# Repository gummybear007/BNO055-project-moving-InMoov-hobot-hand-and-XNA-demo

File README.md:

# BNO055-project-moving-InMoov-hobot-hand-and-XNA-demo
Dont know if that can be usefull for something :)

There are videos how that works:

XNA
https://www.youtube.com/watch?v=5ESsEXsImuc

InMoov
https://www.youtube.com/watch?v=VBxMamMVSek

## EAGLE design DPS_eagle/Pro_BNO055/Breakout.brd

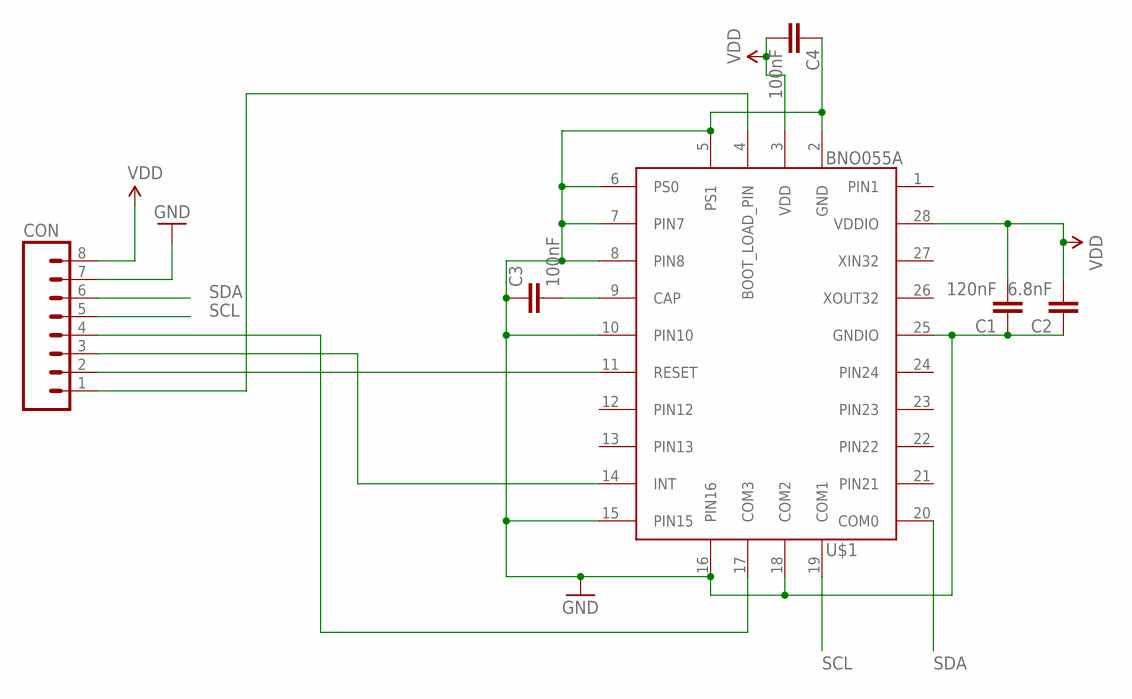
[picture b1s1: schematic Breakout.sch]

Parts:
C1: 120nF; 1206
C2: 6.8nF; 1206
C3, C4: 100nF; 1206
CON: M08NO_SILK; 1X08_NO_SILK
U$1: BNO055A; BNO055

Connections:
GND: C1.1, C2.1, C3.1, C4.1, CON.7, U$1.2 (GND), U$1.5 (PS1), U$1.6 (PS0), U$1.7 (PIN7), U$1.8 (PIN8), U$1.10 (PIN10), U$1.15 (PIN15), U$1.16 (PIN16), U$1.18 (COM2), U$1.25 (GNDIO)
unnamed: CON.2, U$1.11 (RESET)
unnamed: C3.2, U$1.9 (CAP)
unnamed: CON.1, U$1.4 (BOOT_LOAD_PIN)
unnamed: CON.3, U$1.14 (INT)
unnamed: CON.4, U$1.17 (COM3)
SCL: CON.5, U$1.19 (COM1)
SDA: CON.6, U$1.20 (COM0)
VDD: C1.2, C2.2, C4.2, CON.8, U$1.3 (VDD), U$1.28 (VDDIO)

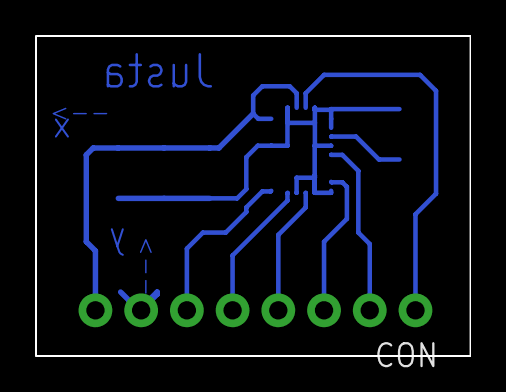
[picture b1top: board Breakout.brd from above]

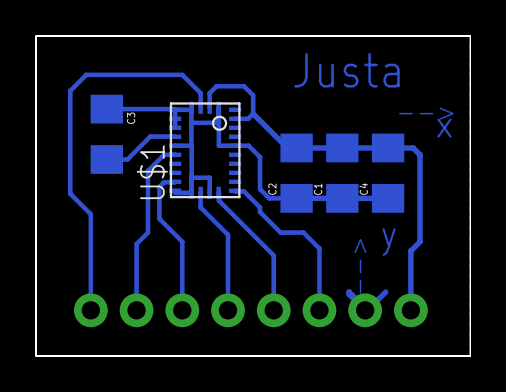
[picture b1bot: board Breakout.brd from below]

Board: 2 copper layers, 24.1 x 17.8 mm, 6 parts (5 on the bottom side), 9 nets.

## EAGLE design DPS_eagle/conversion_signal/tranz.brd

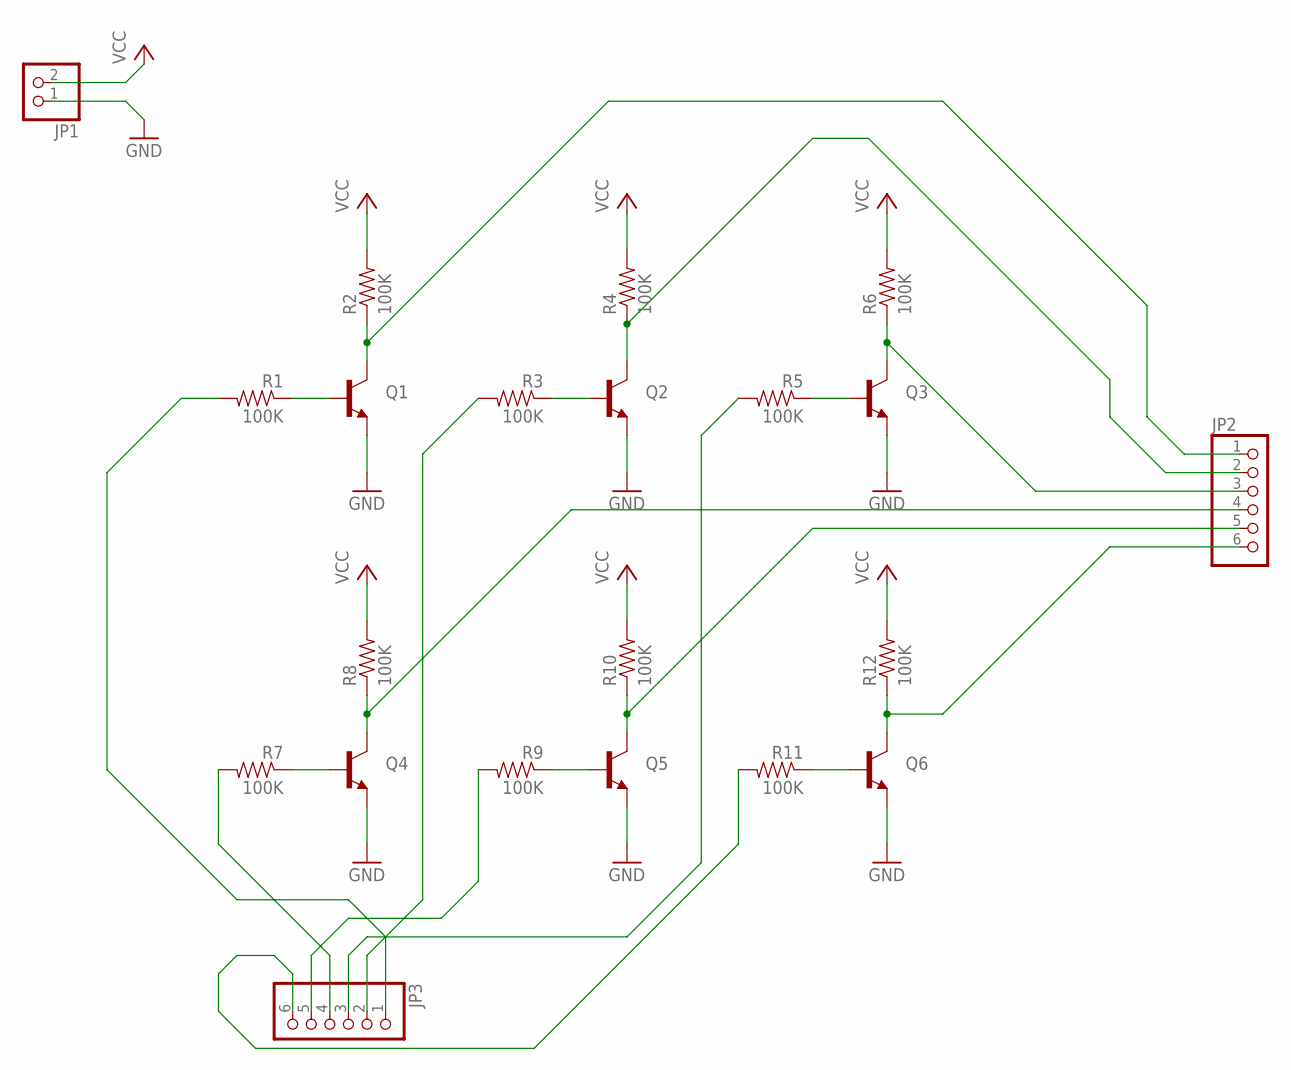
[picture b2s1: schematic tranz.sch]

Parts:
JP1: PINHD-1X2; 1X02
JP2, JP3: PINHD-1X6; 1X06
Q1, Q2, Q3, Q4, Q5, Q6: TRANSISTOR_NPN2N3904; TO-92
R1, R2, R3, R4, R5, R6, R7, R8, R9, R10, R11, R12: 100K; 1206

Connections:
GND: JP1.1, Q1.1 (E), Q2.1 (E), Q3.1 (E), Q4.1 (E), Q5.1 (E), Q6.1 (E)
unnamed: JP3.1, R1.2
unnamed: Q1.2 (B), R1.1
unnamed: JP3.2, R3.2
unnamed: JP3.3, R5.2
unnamed: JP3.4, R7.2
unnamed: JP3.5, R9.2
unnamed: JP3.6, R11.2
unnamed: JP2.1, Q1.3 (C), R2.1
unnamed: JP2.2, Q2.3 (C), R4.1
unnamed: Q2.2 (B), R3.1
unnamed: JP2.3, Q3.3 (C), R6.1
unnamed: Q3.2 (B), R5.1
unnamed: JP2.6, Q6.3 (C), R12.1
unnamed: Q6.2 (B), R11.1
unnamed: Q4.2 (B), R7.1
unnamed: JP2.4, Q4.3 (C), R8.1
unnamed: JP2.5, Q5.3 (C), R10.1
unnamed: Q5.2 (B), R9.1
VCC: JP1.2, R2.2, R4.2, R6.2, R8.2, R10.2, R12.2

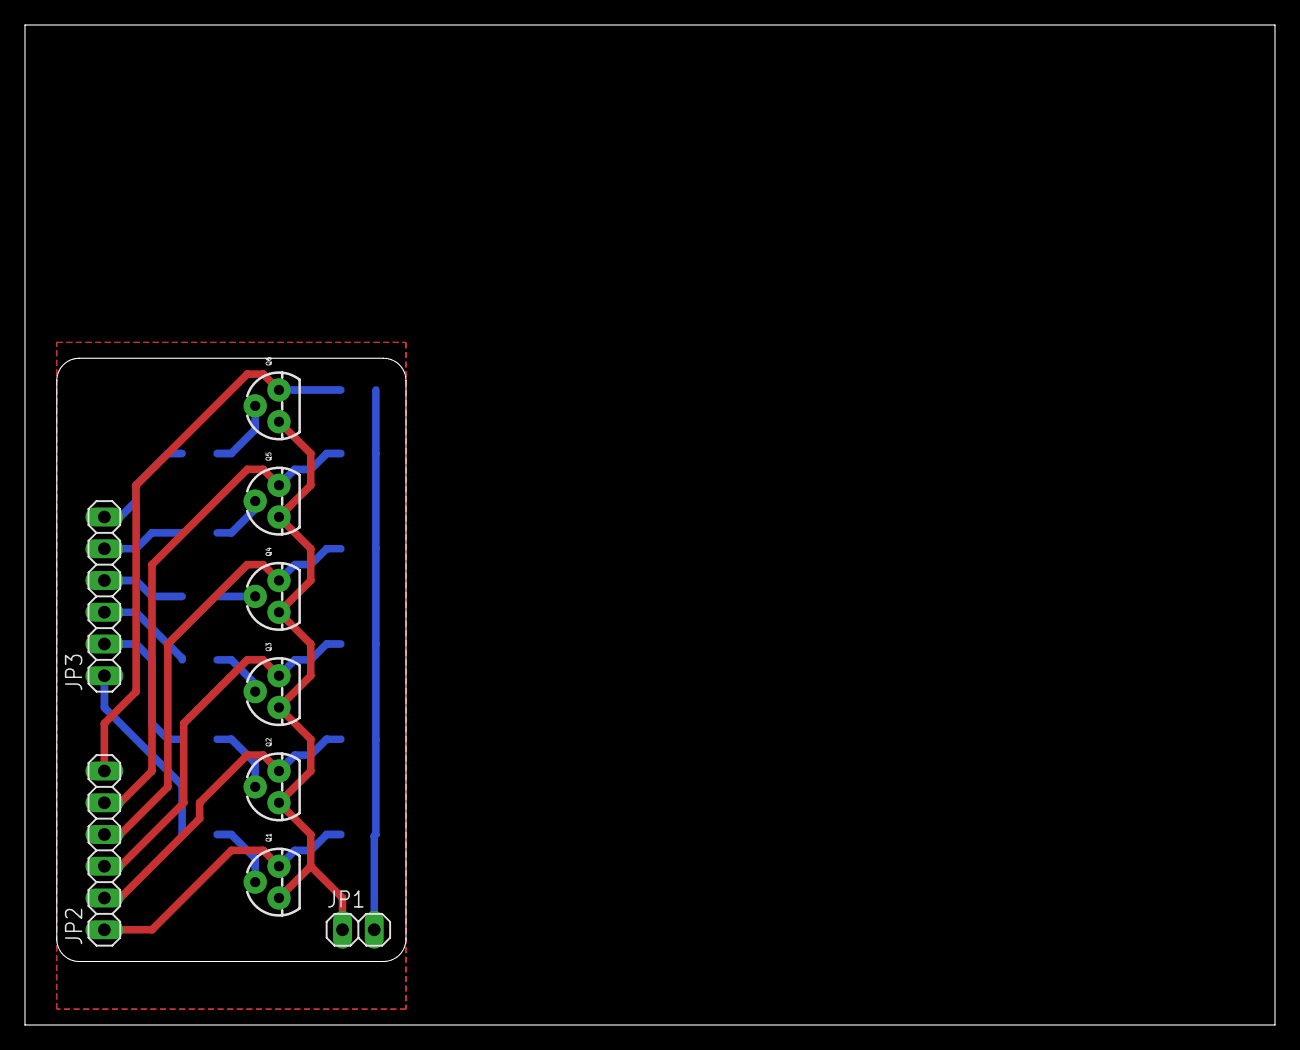
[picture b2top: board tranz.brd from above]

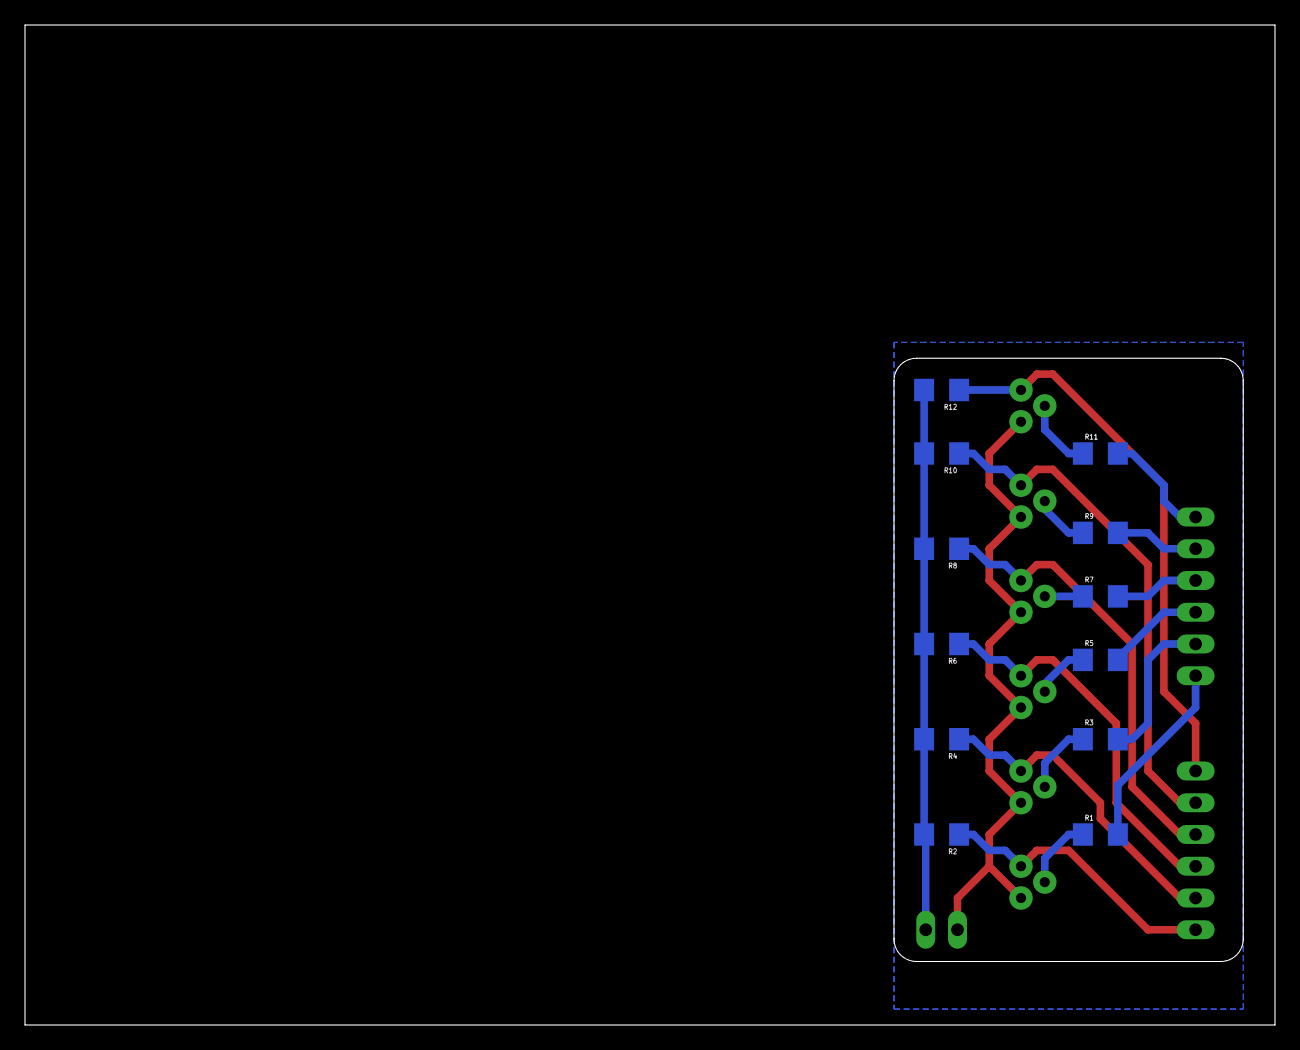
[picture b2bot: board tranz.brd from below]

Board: 2 copper layers, 100.0 x 80.0 mm, 21 parts (12 on the bottom side), 20 nets.

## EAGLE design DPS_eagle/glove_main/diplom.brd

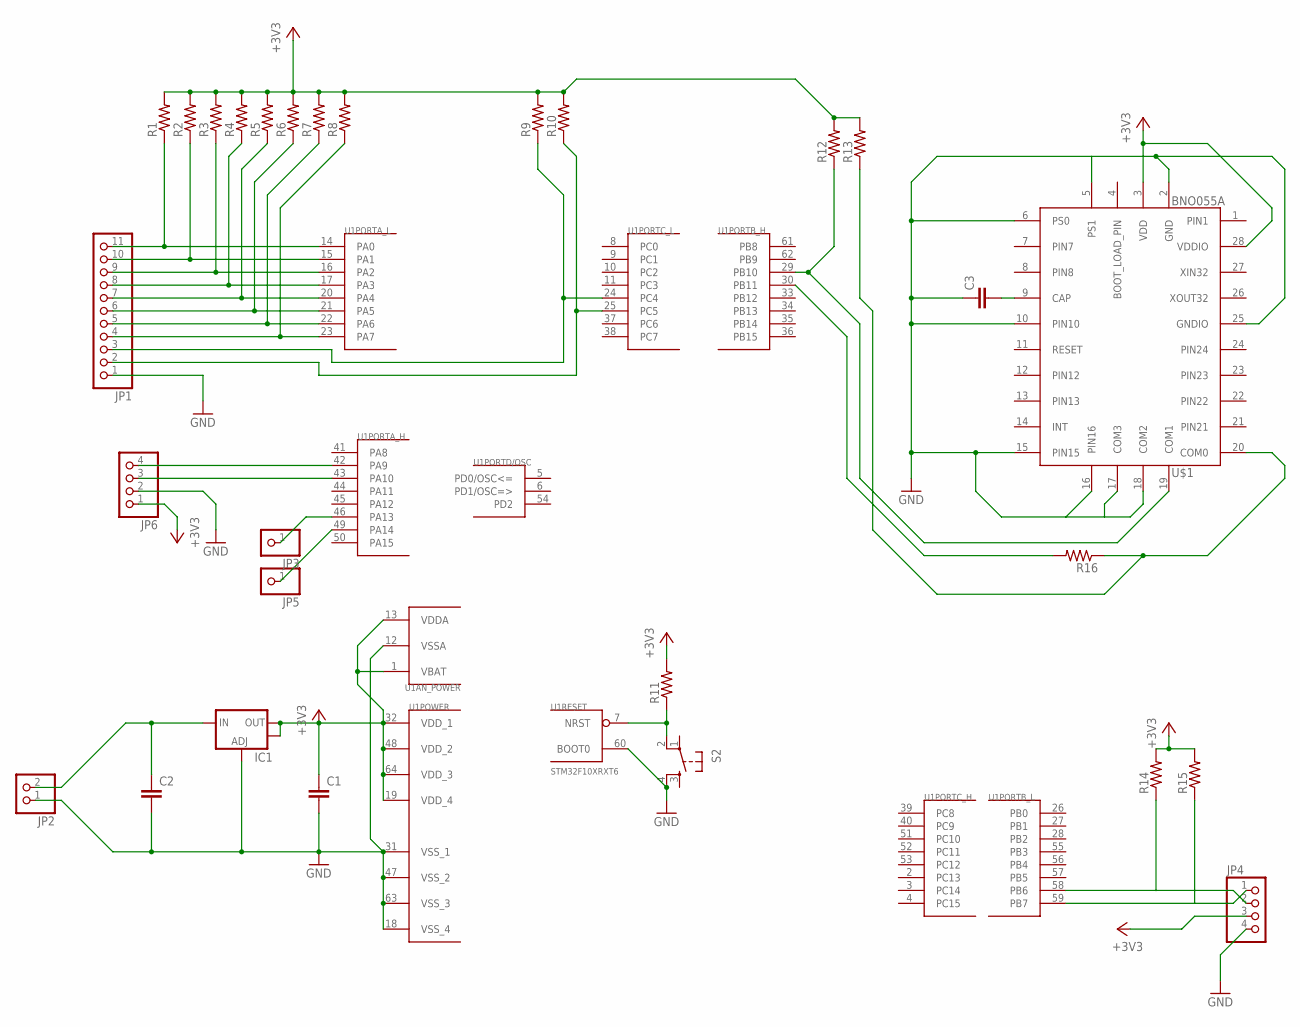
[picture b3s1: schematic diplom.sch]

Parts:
C1, C2, C3: CAP1206; 1206
IC1: V_REG_LM1117SOT223; SOT223
JP1: PINHD-1X11_2.54; 1X11
JP2: PINHD-1X02_2.54; 1X02
JP3, JP5: PINHD-1X01_2.54; 1X01
JP4, JP6: PINHD-1X04_2.54; 1X04
R1, R2, R3, R4, R5, R6, R7, R8, R9, R10, R11, R12, R13, R14, R15, R16: RESISTOR1206; 1206
S2: TAC_SWITCHPTH; TACTILE-PTH
U1: STM32F10XRXT6; TQFP64
U$1: BNO055A; BNO055

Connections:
+3V3: C1.1, IC1.2 (OUT), IC1.4 (OUT), JP4.3, JP6.1, R1.2, R2.2, R3.2, R4.2, R5.2, R6.2, R7.2, R8.2, R9.2, R10.2, R11.2, R12.2, R13.2, R14.2, R15.2, U1.1 (VBAT), U1.13 (VDDA), U1.19 (VDD_4), U1.32 (VDD_1), U1.48 (VDD_2), U1.64 (VDD_3), U$1.3 (VDD), U$1.28 (VDDIO)
GND: C1.2, C2.2, C3.1, IC1.1 (ADJ), JP1.1, JP2.1, JP4.4, JP6.2, S2.4, U1.12 (VSSA), U1.18 (VSS_4), U1.31 (VSS_1), U1.47 (VSS_2), U1.60 (BOOT0), U1.63 (VSS_3), U$1.2 (GND), U$1.5 (PS1), U$1.6 (PS0), U$1.10 (PIN10), U$1.15 (PIN15), U$1.16 (PIN16), U$1.17 (COM3), U$1.18 (COM2), U$1.25 (GNDIO)
unnamed: JP3.1, U1.46 (PA13)
unnamed: JP5.1, U1.49 (PA14)
unnamed: JP1.11, R1.1, U1.14 (PA0)
unnamed: JP1.10, R2.1, U1.15 (PA1)
unnamed: JP1.9, R3.1, U1.16 (PA2)
unnamed: JP1.8, R4.1, U1.17 (PA3)
unnamed: JP1.7, R5.1, U1.20 (PA4)
unnamed: JP1.6, R6.1, U1.21 (PA5)
unnamed: JP1.5, R7.1, U1.22 (PA6)
unnamed: JP1.4, R8.1, U1.23 (PA7)
unnamed: JP1.3, R9.1, U1.24 (PC4)
unnamed: JP1.2, R10.1, U1.25 (PC5)
unnamed: R11.1, S2.2, U1.7 (NRST)
unnamed: C3.2, U$1.9 (CAP)
unnamed: JP4.2, R14.1, U1.58 (PB6)
unnamed: R12.1, U1.29 (PB10), U$1.19 (COM1)
unnamed: R16.2, U1.30 (PB11)
unnamed: C2.1, IC1.3 (IN), JP2.2
unnamed: JP4.1, R15.1, U1.59 (PB7)
unnamed: R13.1, R16.1, U$1.20 (COM0)
unnamed: JP6.4, U1.42 (PA9)
unnamed: JP6.3, U1.43 (PA10)

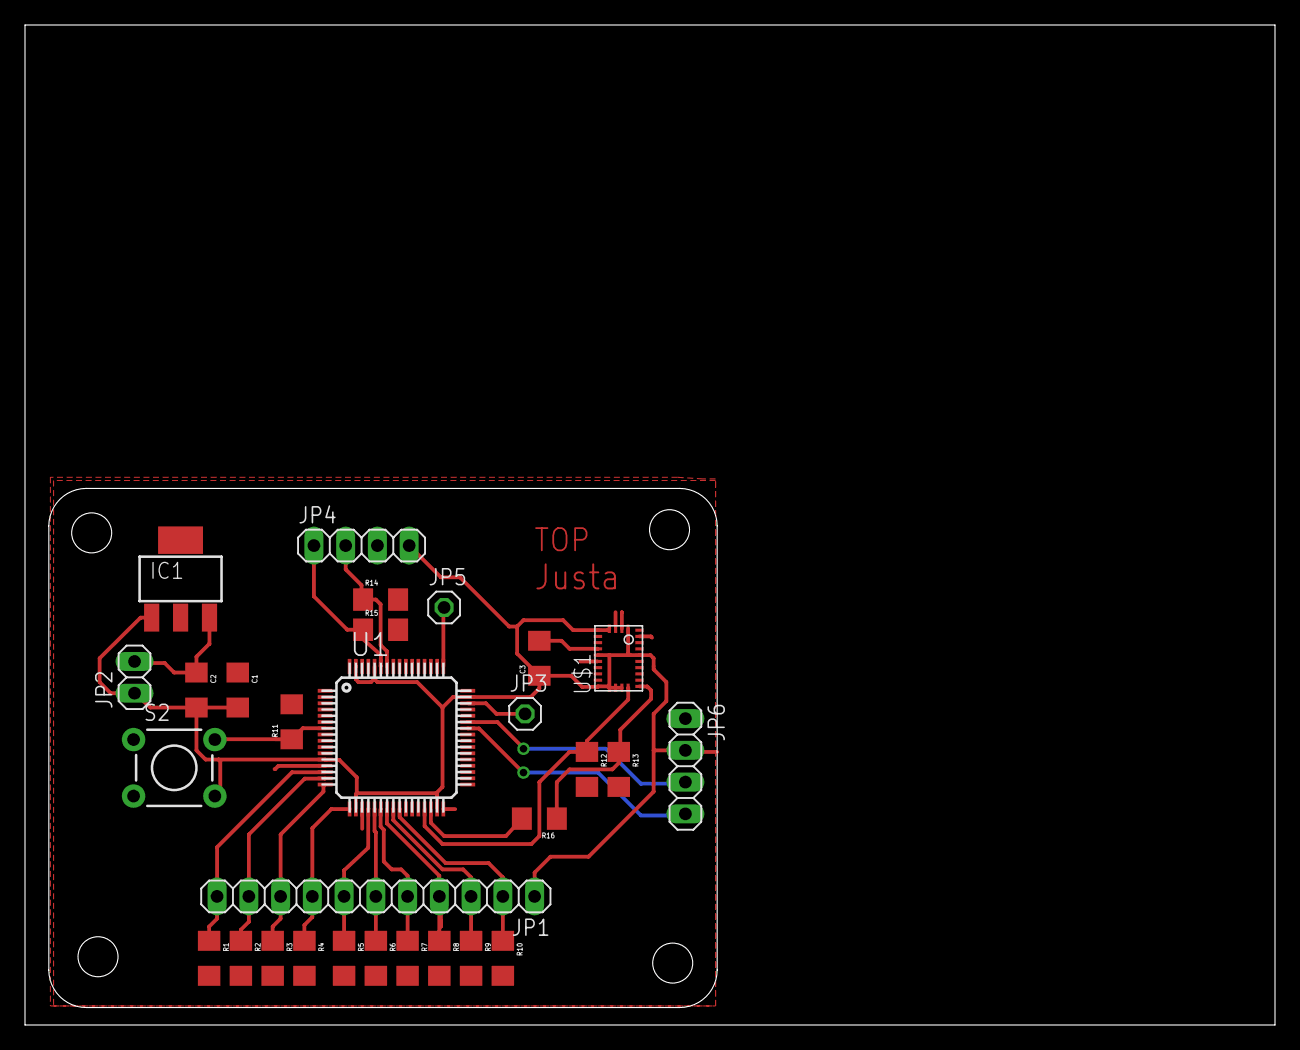
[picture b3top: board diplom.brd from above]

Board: 2 copper layers, 100.0 x 80.0 mm, 29 parts (0 on the bottom side), 24 nets.

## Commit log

2015-08-08 :lollipop: Added .gitattributes & .gitignore files
2015-08-08 Upload code
    contains C# codes (include XNA), C source codes for STM32l1xx, and eagle
    files for creating DPS

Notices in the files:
parts and their libraries:
SparkFun-Capacitors: Licensing: Creative Commons ShareAlike 4.0 International - https://creativecommons.org/licenses/by-sa/4.0
SparkFun: Licensing: CC v3.0 Share-Alike You are welcome to use this library for commercial purposes.
